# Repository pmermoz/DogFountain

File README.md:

Dog Fountain
=========

The Garden's fountain for the dogs based on Arduino

## Introduction

The project started with 2 dogs in a garden and bowls always empty or fill with dirty water. Dogs like fresh water, and two monsters of 100 lbs can consume a lot of water especially under the "hot" California climate.

The first approach was to use an "Outside Faucet Dog Waterer", a mechanical valve put on a faucet and activated by the dog tongue. One dog, the youngest one, try without consistent success and usually finished looking at me for help. The other didn’t even try to look at the valve.

I understand, with some training, both dogs can probably learn how to use a mechanical valve, just I found much more interesting to have a system more intuitive for the dog.

This experience shows:

- It’s not natural for a dog to go near a place where there is no water and push a "button" to get some.
- The youngest dog is always ready to try something new, but the oldest one has apparently some strict manners, and for him a dog should drink from a bowl, not from a faucet.
- When a dog sees water, or hears a water flow, and he is thirsty, he will come to see, and that is without training ;-)

At this point, the only solution was a robot to serve water to the dogs on demand ;-).

Some ideas:

- Start the water when dog approaches to get his attention.
- Avoid to stop the water when dogs are drinking (dog have a moderate sense of humor),
- Stop the water when the dog walks away (bill payer have a moderate sense of humor).
- Have a bowl placed under the faucet to respect “papa” dog habit,
- Try to not overfill the bowl, ideally balance the water output with the dog input.
- Try to have a simple design, simple to build.

## The result

It is now (as July 2014) for almost one year the fountain is online, the dogs use it every day.
I get 2 freezes of the fountain during the year, a simple power off/on solved the problem.

## Build Overview

The fountain is mainly composed of two parts:

* the brain, including CPU, sensors and relay
* the valve and faucet.

The existing wall faucet was too low for the dogs, and too cluttered by hoses. A garden hose is used to deport the fountain.

The fountain faucet is placed on the top of a bowl.

## Components

Components of the Garden's fountain for dogs 

## Water Valve

### Valve location choices

Initially the valve was positioned at the extremity of the hose, but when the valve was closed, the water pressure was expanding the hose… and when the valve open, the elasticity of the hose added to the water pressure was generating a small jet of water...  
and dogs didn’t approve that.

Moving the valve next to the wall faucet solved this inconvenience and we became friend again.

### Analyze of the valve

I used one valve I had in stock, not too expensive and easy to find in store.

This valve is designed for battery powered controller, and gets two stable states.  
A DC current pulse is used to change the state between open and close.   
The polarity of the pulse defines the movement direction: open or close.

By testing this solenoid at various DC voltages, it appears that it could actuate down to 11V DC with a current of about 1.4A.
	
### Current and voltage at the valve when the valve open or close

Note:

* Yellow shows the voltage at the valve  
* Blue shows the current at the valve.

#### Valve open

Notice the pick of back-emf at the end.

If we zoom at the beginning of the pulse:

we can see some fluctuation at the beginning, but nothing really bad.

On the other side, at the end of the pulse, we clearly see a back-emf effect when the current stop

#### Valve Close

### Timing

To estimate the pulse length needed to actuate, I recorded the valve sound and compared for different pulse length the variation of the sound envelop.

#### Valve Open
   
10ms pulse

25ms pulse

50ms pulse

50ms pulse with water flow, without the relay noise. 

Analysis:
* 10ms pulse compared to the 25ms pulse shows missing power in the second part of the sound wave. 10ms is too short.
* On the other side 25ms compared to 50ms does not show any improvement.
* Presence of water flow does not seem to impact duration.

#### Valve Close
  
10ms pulse

25ms pulse

50ms pulse

The close pulse does not show any difference starting at the 10ms pulse.

#### Detail of a 50ms pulse

Following captures show a 50ms pulse during the open and close.  
First, only the relay sound is recorded. In the order: relay 1 open, close, relay 2 open, and close.  
We can verify the time between the relay: open and close is timed to 50ms.

Then, the relay and valve are recorded, with the same sequences.  
We can see much stronger noise created by the valve just after the relay actuates.  
We can also verify the margin between the pulse duration and the valve movement duration.

#### Conclusion

A 20ms pulse should open the valve, and a 10ms pulse should close it.   
Closing the valve is an important step to avoid leak. Better to have a lot of margin here.   
To make it simple, we can set the pulse to 50ms in both directions.   
Open and closing of the valve does not happen often, valve is outside, solenoid temperature should not be a problem.

## Valve Connector

The Orbits valve gets a very small power cable, I needed a little more.  
The valve connects to a male connector not available in store, but creating one is pretty simple.

We use 1/16 (1.6mm) solid wire solder to a 2 wires extension cable.

We add Heat-shrink tubing around the soldering, and use a smaller solid wire to keep the distance between the 2 solid wire pins.


The smaller solid wire is turned around 2 pins providing a rigid assembly.
The pin space between the cable are filled with hot melt glue, using the transversal solid wire for support.


When cold, we cut the two pins to the correct lengths, and smoothing the extremities.
The white cable (positive) connects to the open pin of the Orbit connector.

Waterproofing needs to be added.

## Valve Relay

The relays are used to commute the valve. It is a simple solution to commute 12V 1.5A.  
Each relay gets a contact normally-open and normally-close. Pulling to low IN1 or IN2 switch the relay.   
Two relays are needed to generate 3 states: Open Pulse, Close Pulse, and Stay.

### Valve Connection to Relay

The following table describes the action or the relay input on the valve:

 IN1	| IN2   | Open Pin | Close Pin | State | Description
--------|-------|----------|-----------|-------|----
 Low	| Low	| 12V		| 12V		| Stay | Keep valve state (not used)
 Low	|	High|	12V		| GND		| Open Pulse | Valve switch to Open
 High	|	Low	| GND		|	12V		| Close Pulse | Valve switch to close 
 High	| High	| GND		|	GND		| Stay  | Keep valve state

Reference:
* [wikipedia](http://en.wikipedia.org/wiki/Relay/)

## Fountain Sensor: Proximity

The HC-SR04 Ultrasonic sensor is inexpensive and popular. It can determine the distance of an  object from 2cm (1”) to 3m (10ft) or more.  
The detection area is very narrow, about 2 degrees.

This sensor emits an ultrasonic sound (ping) and the time for the echo to come back gives the distance, like an active sonar.

This sensor gets few drawbacks:
* It is an active sensor, not sure how long before it will fail with continues operation.
* False positive if a fly is moving on the front of the sensor.
* Dog seems to hear the ultrasonic sound, and they might ignore if present continuously.

And some good sides:
* Dogs hear the ultrasonic sound, they can associate the sound with "Hey! Remember! Water is here!”.
* The sensor returns a distance, perfect to fine control of the valve activation.

Reference:
* [wikipedia](http://en.wikipedia.org/wiki/Sonar#Active_sonar)

## Fountain Sensor: PIR

PIR is also inexpensive and popular. It can sense motion of human or animal (heat source) up to 6m (20 ft).  
The detection area is wide, almost 180 degrees.

This sensor gets few drawback:
* It detects only movement of heat source, when the movement stops (dog drinking) the detection also stops.
* The PIR is sensitive to a lot of unwanted type of heat movement, like a flow of hot air, or the cloud that creates moving sun ray on the ground. Outside a PIR can generate a lot of false positive detection.
* Also the PIR gives a very basic information (movement detected) but lack details like the direction of the movement or if the dog is currently drinking, that will make difficult to optimize the water usage.

And some good sides:
* Passive, silence, and probably long life. Does not disturb the environment.
* Large detection area, can see the dog coming from far.

References:
* [wikipedia](http://en.wikipedia.org/wiki/Passive_infrared_sensor)
* [ladyada](http://www.ladyada.net/learn/sensors/pir.html)

## Sensors usage

The idea is to use a tandem of two sensors to detect dog presence and trigger the water flow.

Using a combination of both sensor can improve the detection:
- Initially the ultrasonic sensor is turned off.
- The PIR sensor “scans” the region around the fountain.
- When a dog approaches, the PIR detects the movement and the Ultrasonic sensor starts.
- When the dog reaches the fountain, the Ultrasonic sensor triggers the water fountain
- When the dog leaves, the Ultrasonic sensor triggers the fountain stop
- After a while, if no more movement, the PIR stops the Ultrasonic sensor.  

## Feedback: RGB LED

The LED is very useful to debug the fountain code.  
At night the box is glowing with a pulsing white light when the fountain sleeps... very nice effect.

The RGB led provides the following feedback (in order):

Light	| Description
--------|----------
Green | Near presence detected (ultrasonic)
Yellow (Red+Green) | Far presence detected (ultrasonic debug)
Red	| Motion detected (PIR)
Blue | PIR was recently triggered, but no more
White pulsing | Fountain is sleeping
Black | Do you have power?

Note: 
* The table order indicates what will be the feedback if multiple sensors are trigged at the same time, for example if we have both the PIR and ultrasonic, then we will get only the Ultrasonic indication.
* The white pulsing appears if nothing else is present.

The Arduino Nano can provide up to 40mA for each pin. 

We do not need the usual 20mA per LED, 9mA should be enough for our usage.
From the measure of the forward voltage for each color, we get the value for each resistor

Color | FV | ohm
------|---:|----:
Red   |1.7V|180
Green |2.4V|100
Blue  |2.5V|100

## CPU

The fountain is based on an Arduino nano, small and inexpensive.

References: 
* [Arduino](http://arduino.cc)

## Fountain Body

The COSTCO Band-aid box fits very nicely for the purpose.  
The good size, and the compartments inside fit the Arduino and relay almost perfectly. 

## Power Supply

A standard power supply is used, and a connector is added to the bottom of the box.

Note: The same connector is used to connect to the valve.

## Schematic

The schema is pretty simple, few soldering are needed.  

A capacitor (470µF) was added to the power line energizing the valve.  
The capacitor provides a reserve of energy for the valve, and removes all visible back-emf to the power line.  
Without the capacitor, the Arduino is completely unstable.

Note: the capacitor cannot be place directly on the valve because of the valve inversion of polarity.  

Most connections use Female to Female jumper cable.

The “hat” is a cut from a plastic envelope, fixed on the top of a Band-Aid box.  
That was nice looking hat... but after a year the plastic didn't survive the sun :(

## Parts and Cost

Description | Reference | Quantity | Price | Store
------------|-----------|---------:|------:|:-----:
CPU | Arduino Nano v3.0 | 1 | $13.99 | [Amazon](http://www.amazon.com/SainSmart-Nano-v3-0-for-Arduino/dp/B00761NDHI/ref=sr_1_2?ie=UTF8&qid=1382742241&sr=8-2&keywords=arduino+nano)
Valve| Orbit extra valve | 1 | $13.56 | [Amazon](http://www.amazon.com/Orbit-58874N-Extra-Complete-Watering/dp/B003LY4I2I/ref=pd_sim_lg_2)
Sensor | 2-Channel Relay Module | 1 | $7.18 | [Amazon](http://www.amazon.com/SainSmart-2-CH-2-Channel-Relay-Module/dp/B0057OC6D8/ref=sr_1_1?ie=UTF8&qid=1382743142&sr=8-1&keywords=sainsmart+relay+module+2)
Power Supply | DC 12V 1.5A | 1 | $7.00 |
Connector| 2.1mmx5.5mm DC Power Jack Socket Female | 2 | $5.32 | [Amazon](http://www.amazon.com/gp/product/B00JR591DG/ref=ox_sc_act_title_1?ie=UTF8&psc=1&smid=A1THAZDOWP300U)
Sensor | HC-SR04 Ultrasonic Distance Sensor | 1 | $3.13 | [Amazon](http://www.amazon.com/SainSmart-HC-SR04-Ranging-Detector-Distance/dp/B004U8TOE6/ref=sr_1_1?ie=UTF8&qid=1382741804&sr=8-1&keywords=sr04)
Sensor | HC-SR501 Human Sensor Module Pyroelectric Infrared | 1 | $2.67 | [Amazon](http://www.amazon.com/HC-SR501-Sensor-Module-Pyroelectric-Infrared/dp/B007XQRKD4/ref=pd_bxgy_e_text_y)
Component| Resistors: 1x 180 ohm, 2x 100 ohm| 3 | $0.10 |
Component| RGB Led ($2.67/50)| 1 | $0.05 | [Amazon](http://www.amazon.com/gp/product/B005VMDROS)
Component| Capacitor | 1 | $0.03 | [Amazon](http://www.amazon.com/Joe-Knows-Electronics-Value-Capacitor/dp/B007SVHFXO/ref=sr_1_4?ie=UTF8&qid=1382742843&sr=8-4&keywords=capacitor)
Cable | 20cm Female to Female 2.54mm 0.1 Inch Jumper Cable Wires Connector ($3.99/5)| 1 | $0.80 | [Amazon](http://www.amazon.com/gp/product/B00D8WOWMY)
Box| COSTCO’s Band-Aid (Recycling) | 1 | $0.00 | COSTCO
***Total*** | | | ***$53.83*** |

<!--| DC Power connector 2.1mm x 5.5mm Female | 2 | $7.00 | [Radioshack](http://www.radioshack.com/product/index.jsp?productId=2102486)-->

## Prototype & Test

Testing the PIR and Ultrasonic distance sensor.

First prototype and it's beautiful box  :)  
Notice the relay directly connected to the wall faucet.

Test of all components before integration.

Testing a configuration of the fountain faucet. The valve and the "jet" effect.

#### Testing of the valve

A simple setup to test the valve. The valve is controlled by 2 switches.

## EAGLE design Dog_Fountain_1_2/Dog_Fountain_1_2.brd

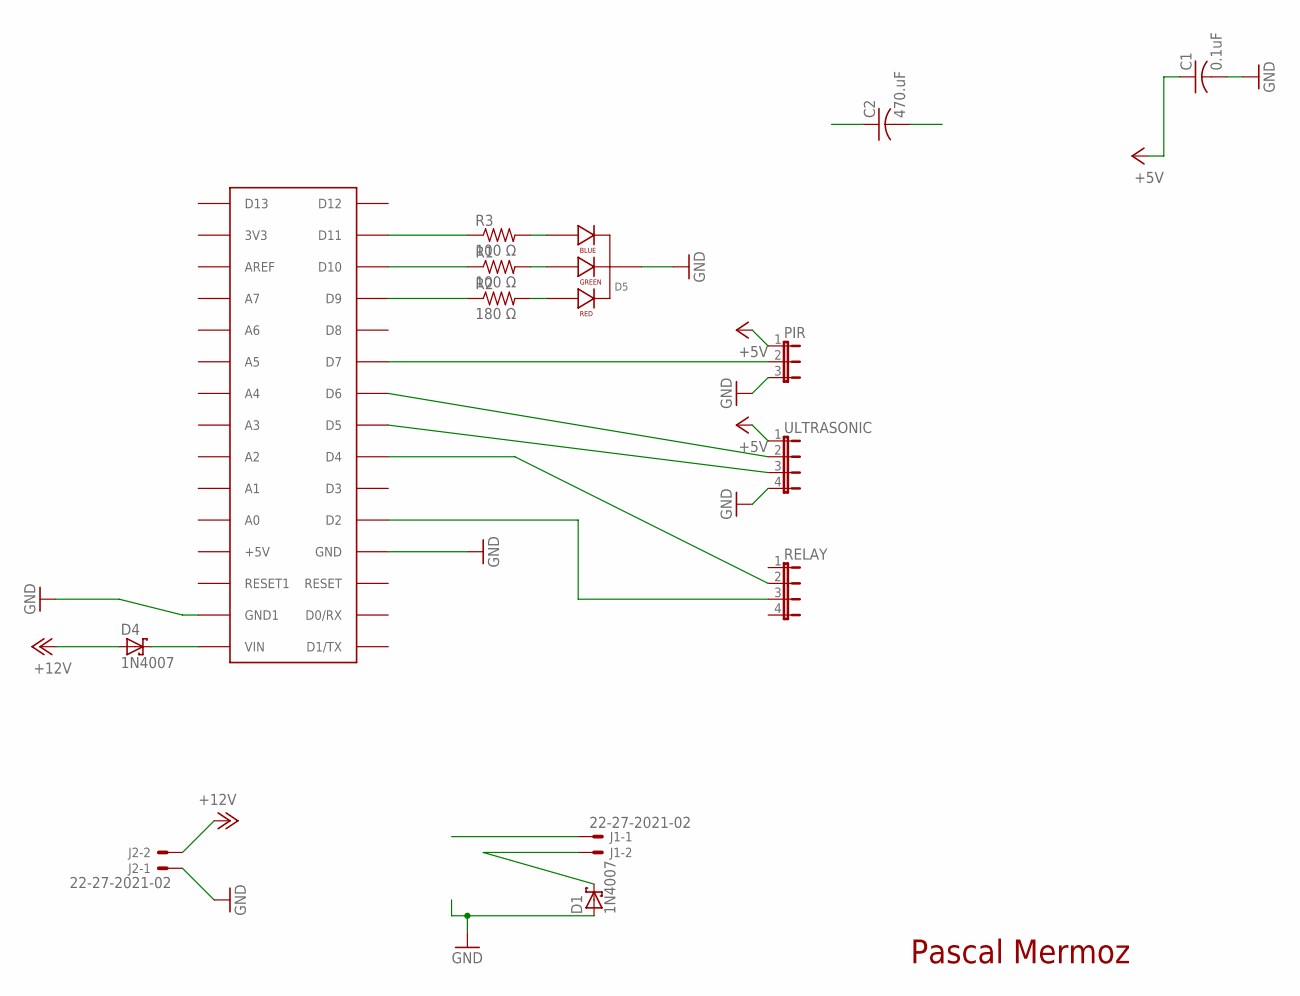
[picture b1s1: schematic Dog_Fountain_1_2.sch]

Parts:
C1: 0.1uF; C050-024X044; MPN C317C104K5R5TA
C2: 470.uF; C050-024X044; MPN C317C104K5R5TA
D1, D4: 1N4007; DO41-7.6; MPN KBP202G
D5: LED-RGB-CC-THRUDIFFUSE; LED-RGB-THRU
J1, J2: 22-27-2021-02; 6410-02
PIR: JP2E; JP2
R1, R3: 100 Ω; 0204V
R2: 180 Ω; 0204V
RELAY: JP4E; JP4
U$1: ARDUINONANO; PDIP-32; MPN A000005
ULTRASONIC: JP4E; JP4

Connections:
+5V: C1.1, PIR.1, ULTRASONIC.1
+12V: D4.A, J2.2
GND: C1.2, D1.A, D5.2 (CATHODE), J2.1, PIR.3, U$1.GND1, ULTRASONIC.4
unnamed: D1.C, J1.2
unnamed: R3.1, U$1.D11
unnamed: R1.1, U$1.D10
unnamed: R2.1, U$1.D9
unnamed: RELAY.2, U$1.D4
unnamed: D5.1 (RED_CATHODE), R2.2
unnamed: D5.3 (GREEN_CATHODE), R1.2
unnamed: D5.4 (BLUE_CATHODE), R3.2
unnamed: RELAY.3, U$1.D2

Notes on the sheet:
Pascal Mermoz

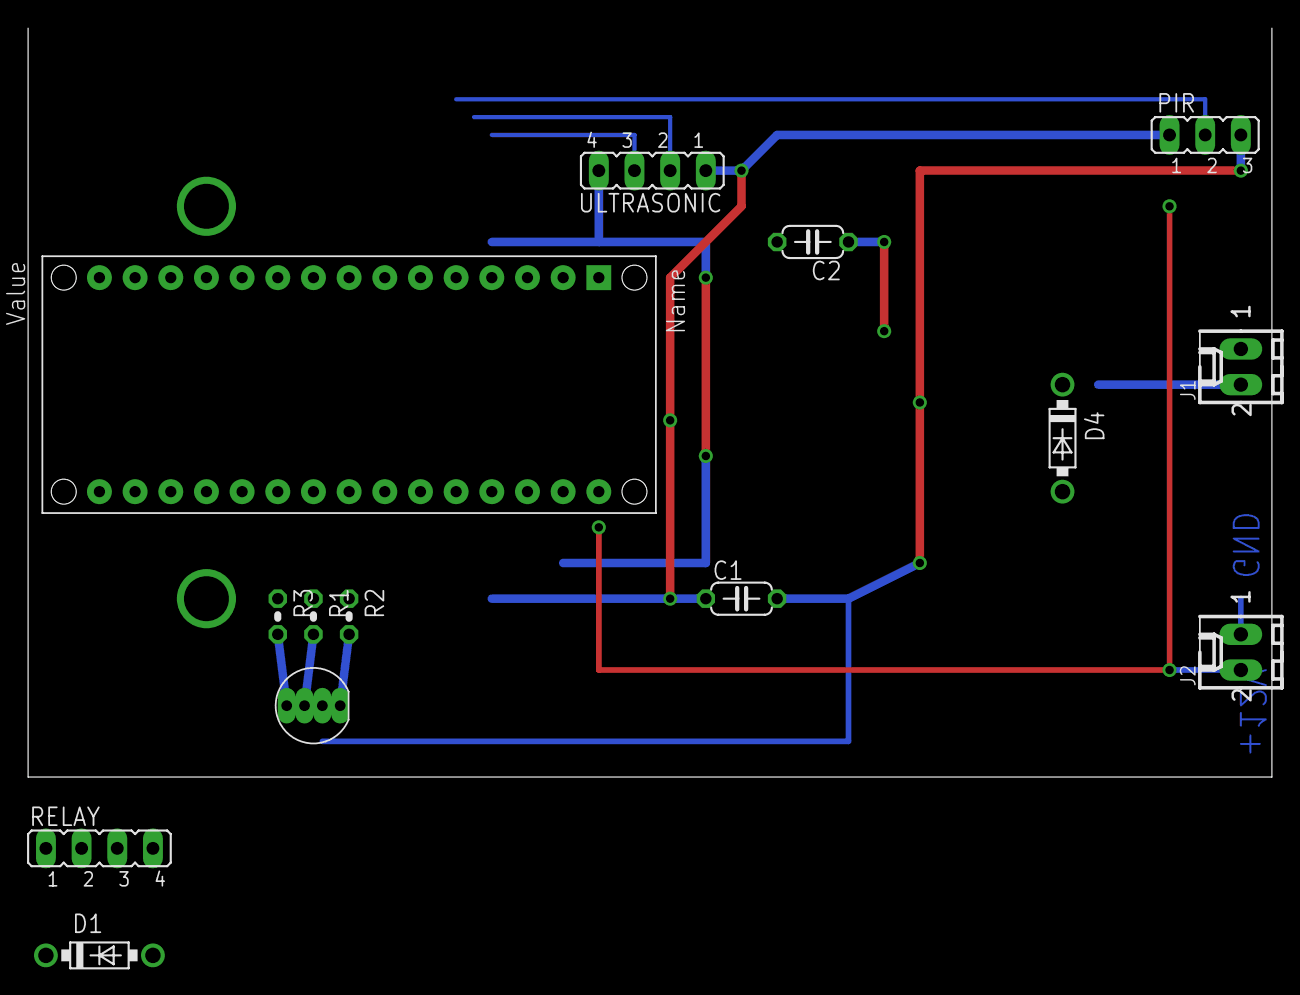
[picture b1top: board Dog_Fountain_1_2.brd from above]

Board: 2 copper layers, 88.6 x 53.3 mm, 14 parts (0 on the bottom side), 12 nets.

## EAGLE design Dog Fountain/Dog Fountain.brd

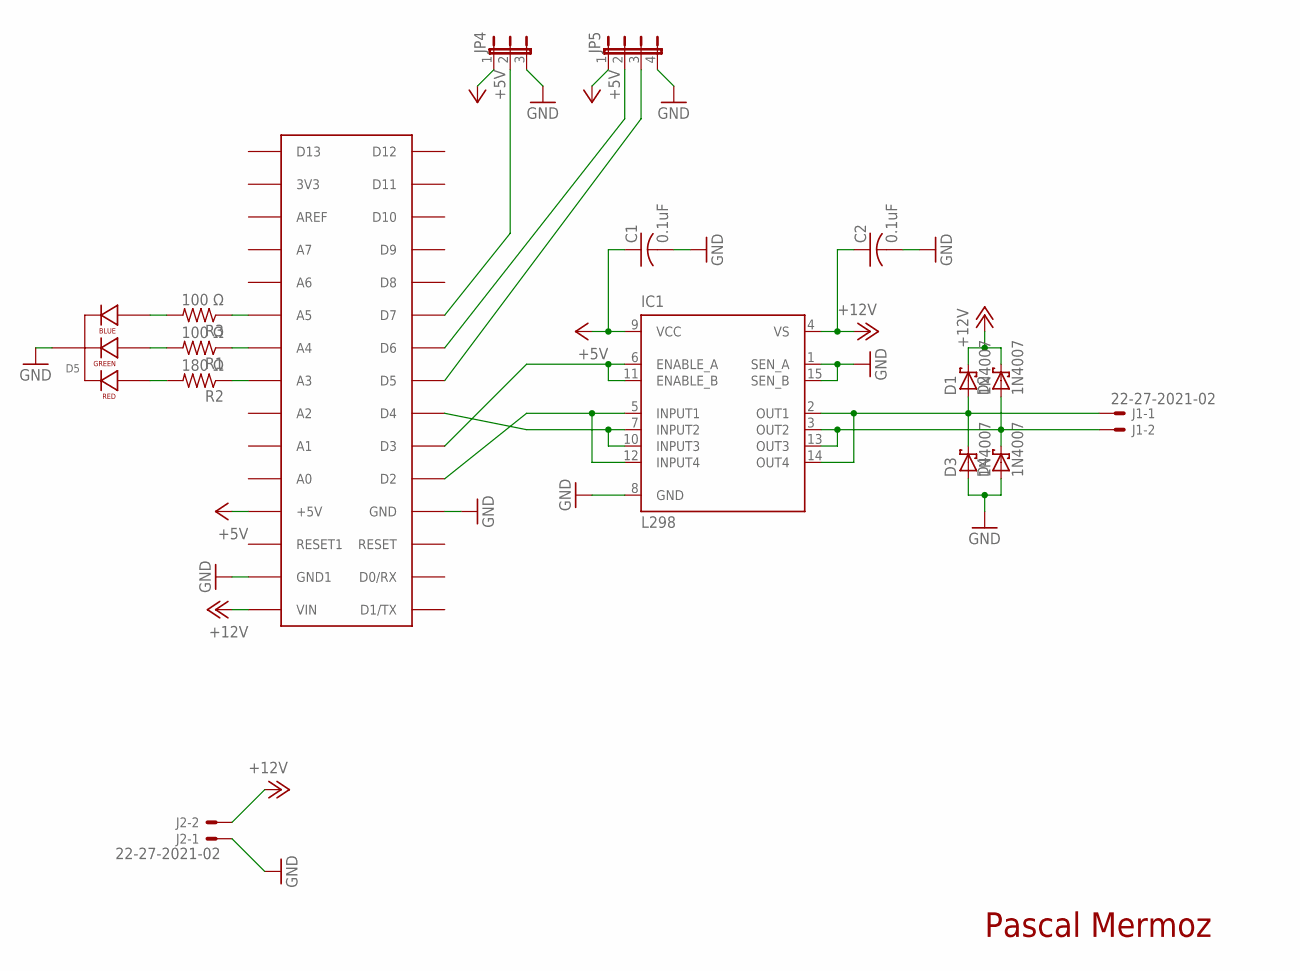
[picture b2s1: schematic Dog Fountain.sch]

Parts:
C1, C2: 0.1uF; C050-024X044; MPN C317C104K5R5TA
D1, D2, D3, D4: 1N4007; DO41-7.6; MPN KBP202G
D5: LED-RGB-CC-THRUDIFFUSE; LED-RGB-THRU
IC1: L298; MULTIWATT-15
J1, J2: 22-27-2021-02; 6410-02
JP4: JP2E; JP2
JP5: JP4E; JP4
R1, R3: 100 Ω; 0204V
R2: 180 Ω; 0204V
U$1: ARDUINONANO; PDIP-32; MPN A000005

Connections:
+5V: C1.1, IC1.9 (VCC), JP4.1, JP5.1, U$1.+5V
+12V: C2.1, D1.C, D2.C, IC1.4 (VS), J2.2, U$1.VIN
GND: C1.2, C2.2, D3.A, D4.A, D5.2 (CATHODE), IC1.1 (SEN_A), IC1.8 (GND), IC1.15 (SEN_B), J2.1, JP4.3, JP5.4, U$1.GND, U$1.GND1
unnamed: IC1.6 (ENABLE_A), IC1.11 (ENABLE_B), U$1.D3
unnamed: IC1.5 (INPUT1), IC1.12 (INPUT4), U$1.D2
unnamed: D2.A, D4.C, IC1.3 (OUT2), IC1.13 (OUT3), J1.2
unnamed: D1.A, D3.C, IC1.2 (OUT1), IC1.14 (OUT4), J1.1
unnamed: IC1.7 (INPUT2), IC1.10 (INPUT3), U$1.D4
unnamed: JP4.2, U$1.D7
unnamed: JP5.2, U$1.D6
unnamed: JP5.3, U$1.D5
unnamed: R3.1, U$1.A5
unnamed: R1.1, U$1.A4
unnamed: R2.1, U$1.A3
unnamed: D5.1 (RED_CATHODE), R2.2
unnamed: D5.3 (GREEN_CATHODE), R1.2
unnamed: D5.4 (BLUE_CATHODE), R3.2

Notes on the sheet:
Pascal Mermoz

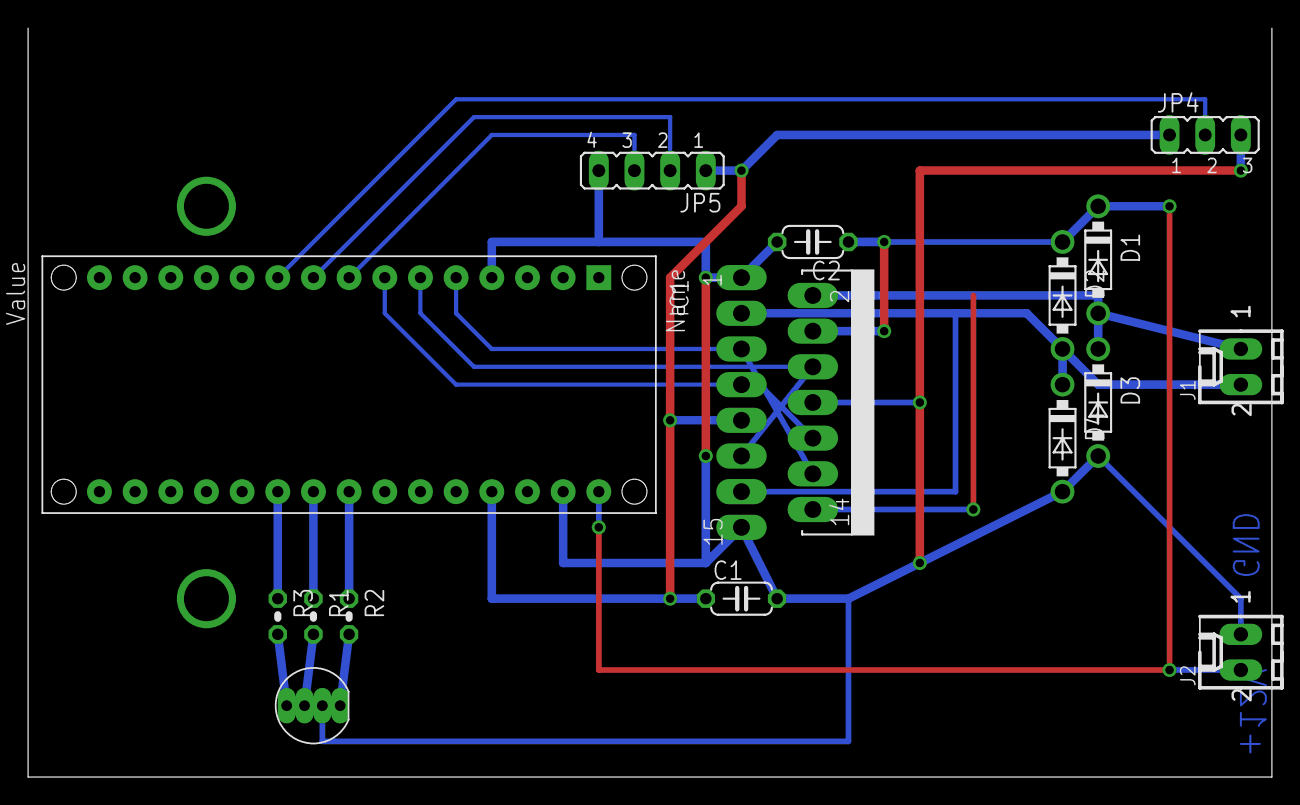
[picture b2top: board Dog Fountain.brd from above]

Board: 2 copper layers, 88.6 x 53.3 mm, 16 parts (0 on the bottom side), 17 nets.

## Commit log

2013-07-26 Initial checkin
2013-08-03 PCB board first test
2013-08-03 - Change AnalogWrite to DigitalWrite (no PWM on Analog pin) - Fix pin assignment
2013-08-10 Another try with 12v power supply
2013-08-18 Drop PCB board, use 12v power supply, relay, and Dupont connector. Get a pulse white light, change detection logic.
2013-10-15 - Remove time extension upon fare distance detection - Change feedback: yellow for fare detection
2013-10-15 - Sonar detection extended from 2.5s to 5s - Sleep pulse light extends from 5s to 6s period
2014-02-03 - cleanup - documentation (WIP)
2014-07-19 cleanup
2014-08-01 Add doc
2014-08-05 Add animated GIF to show the fountain light

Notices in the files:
parts and their libraries:
SparkFun-LED: Licensing: CC v3.0 Share-Alike You are welcome to use this library for commercial purposes.
